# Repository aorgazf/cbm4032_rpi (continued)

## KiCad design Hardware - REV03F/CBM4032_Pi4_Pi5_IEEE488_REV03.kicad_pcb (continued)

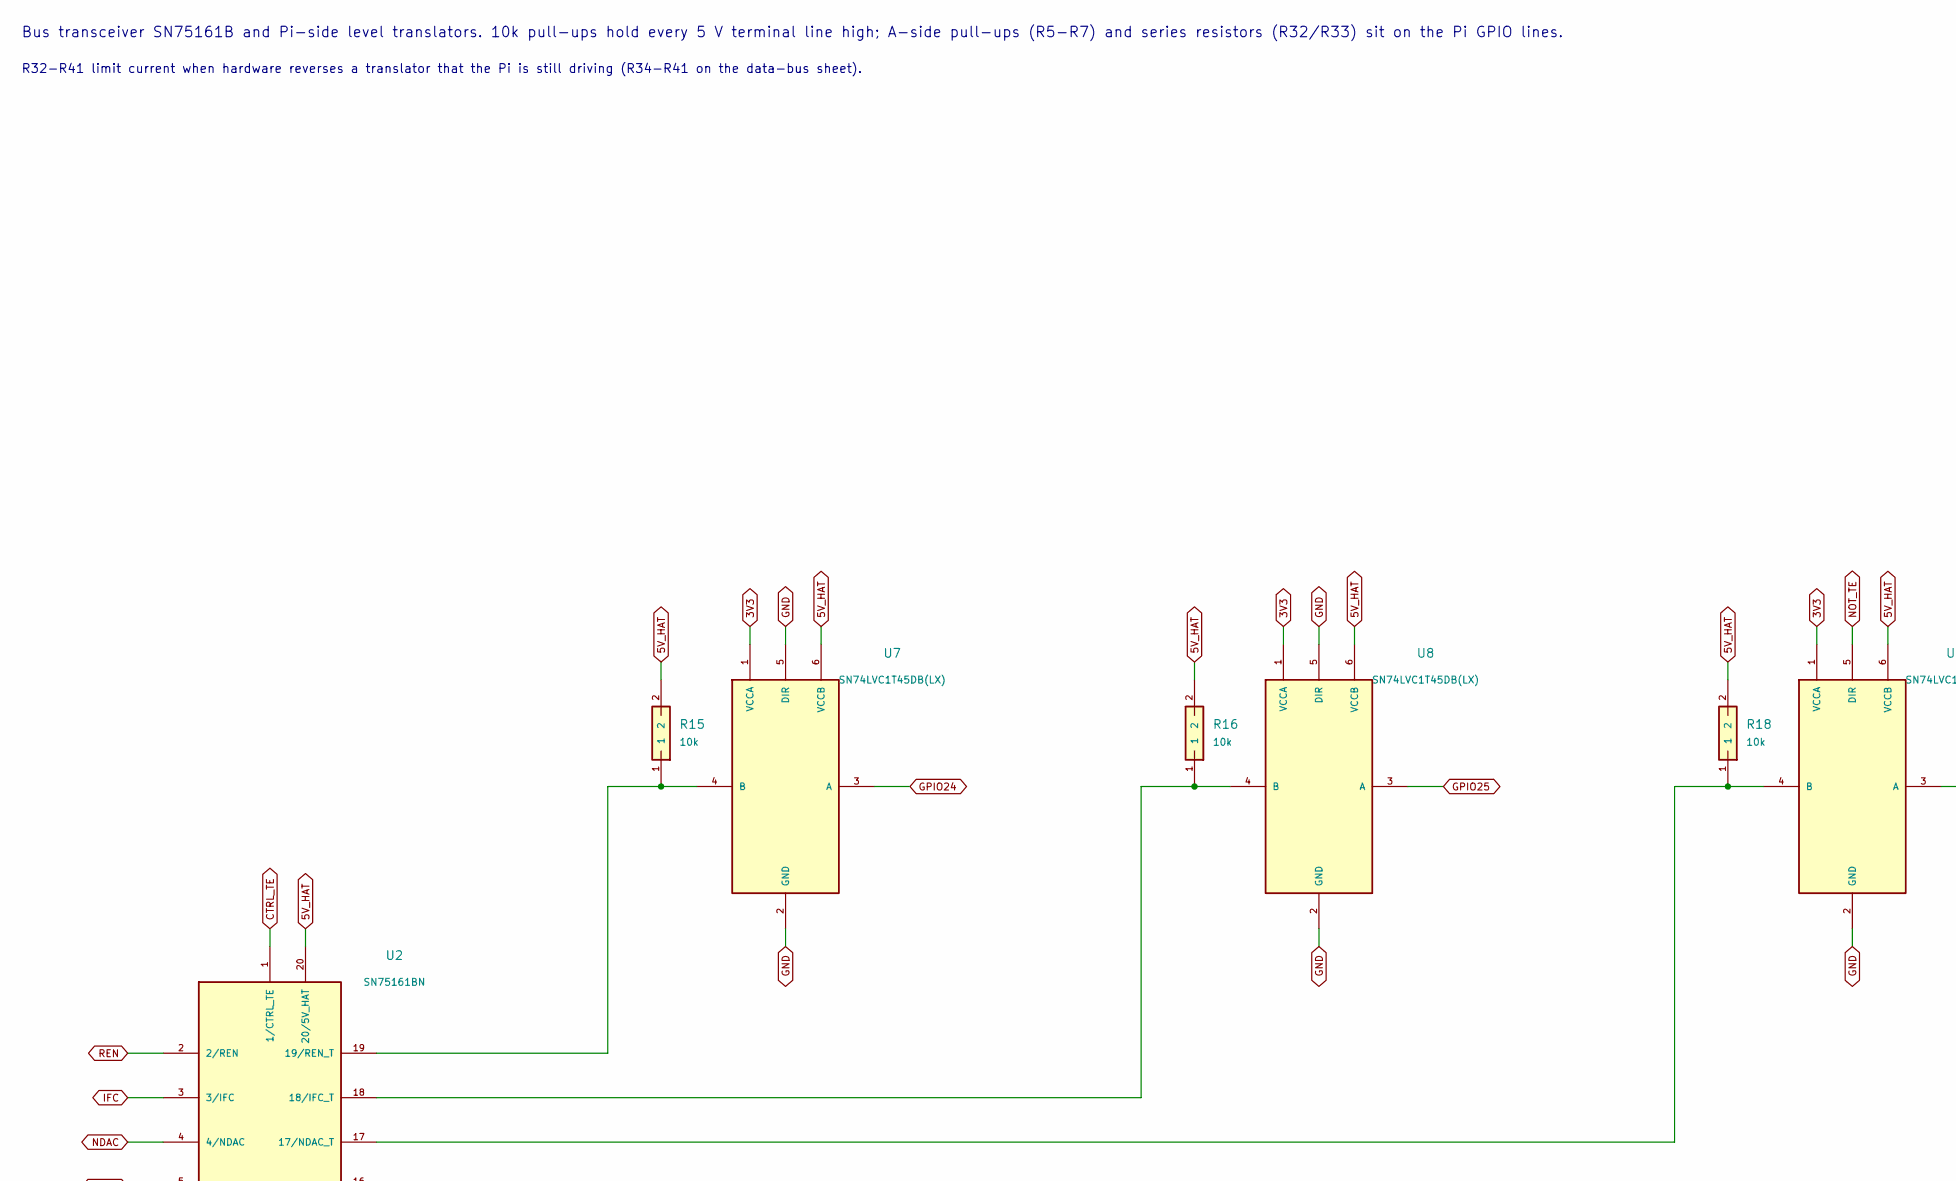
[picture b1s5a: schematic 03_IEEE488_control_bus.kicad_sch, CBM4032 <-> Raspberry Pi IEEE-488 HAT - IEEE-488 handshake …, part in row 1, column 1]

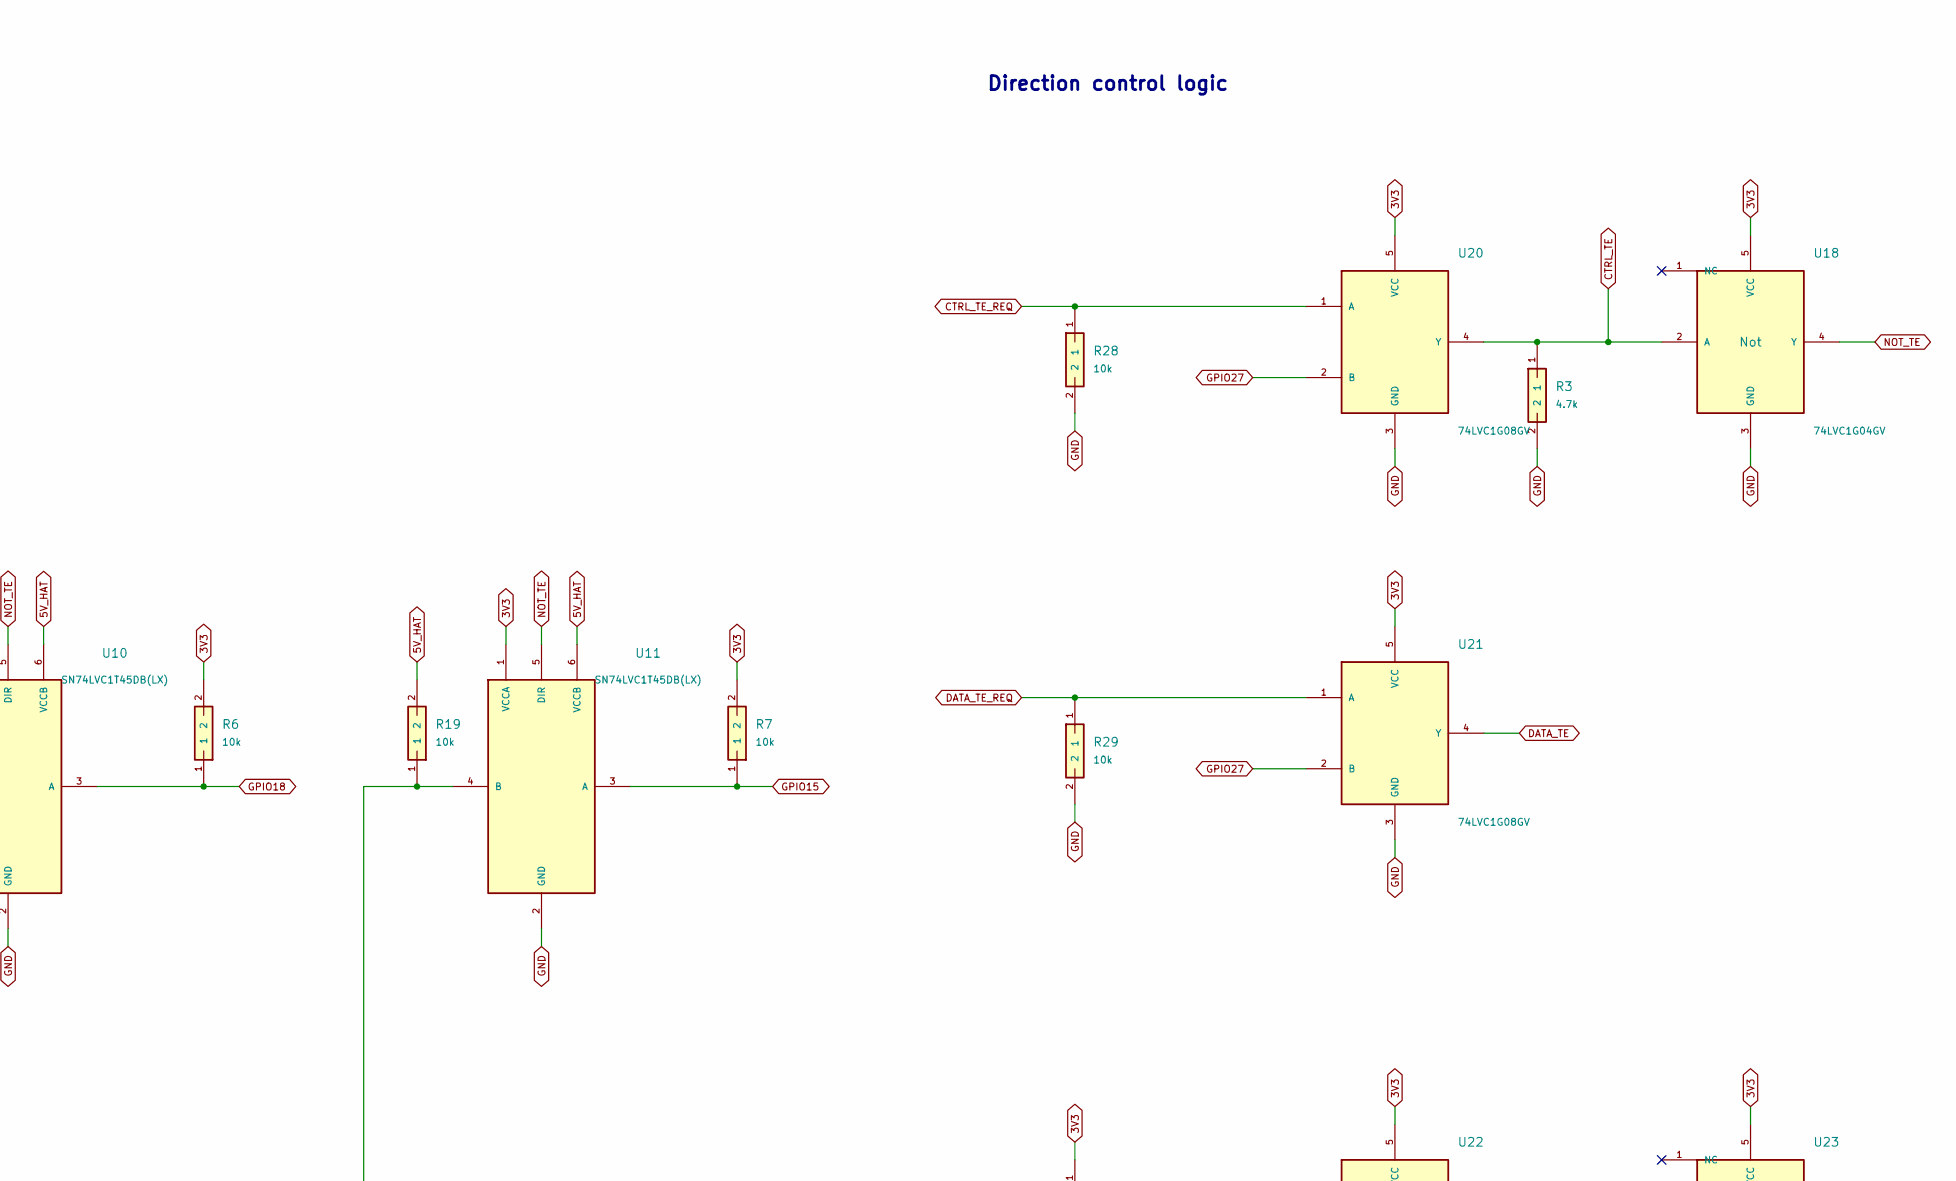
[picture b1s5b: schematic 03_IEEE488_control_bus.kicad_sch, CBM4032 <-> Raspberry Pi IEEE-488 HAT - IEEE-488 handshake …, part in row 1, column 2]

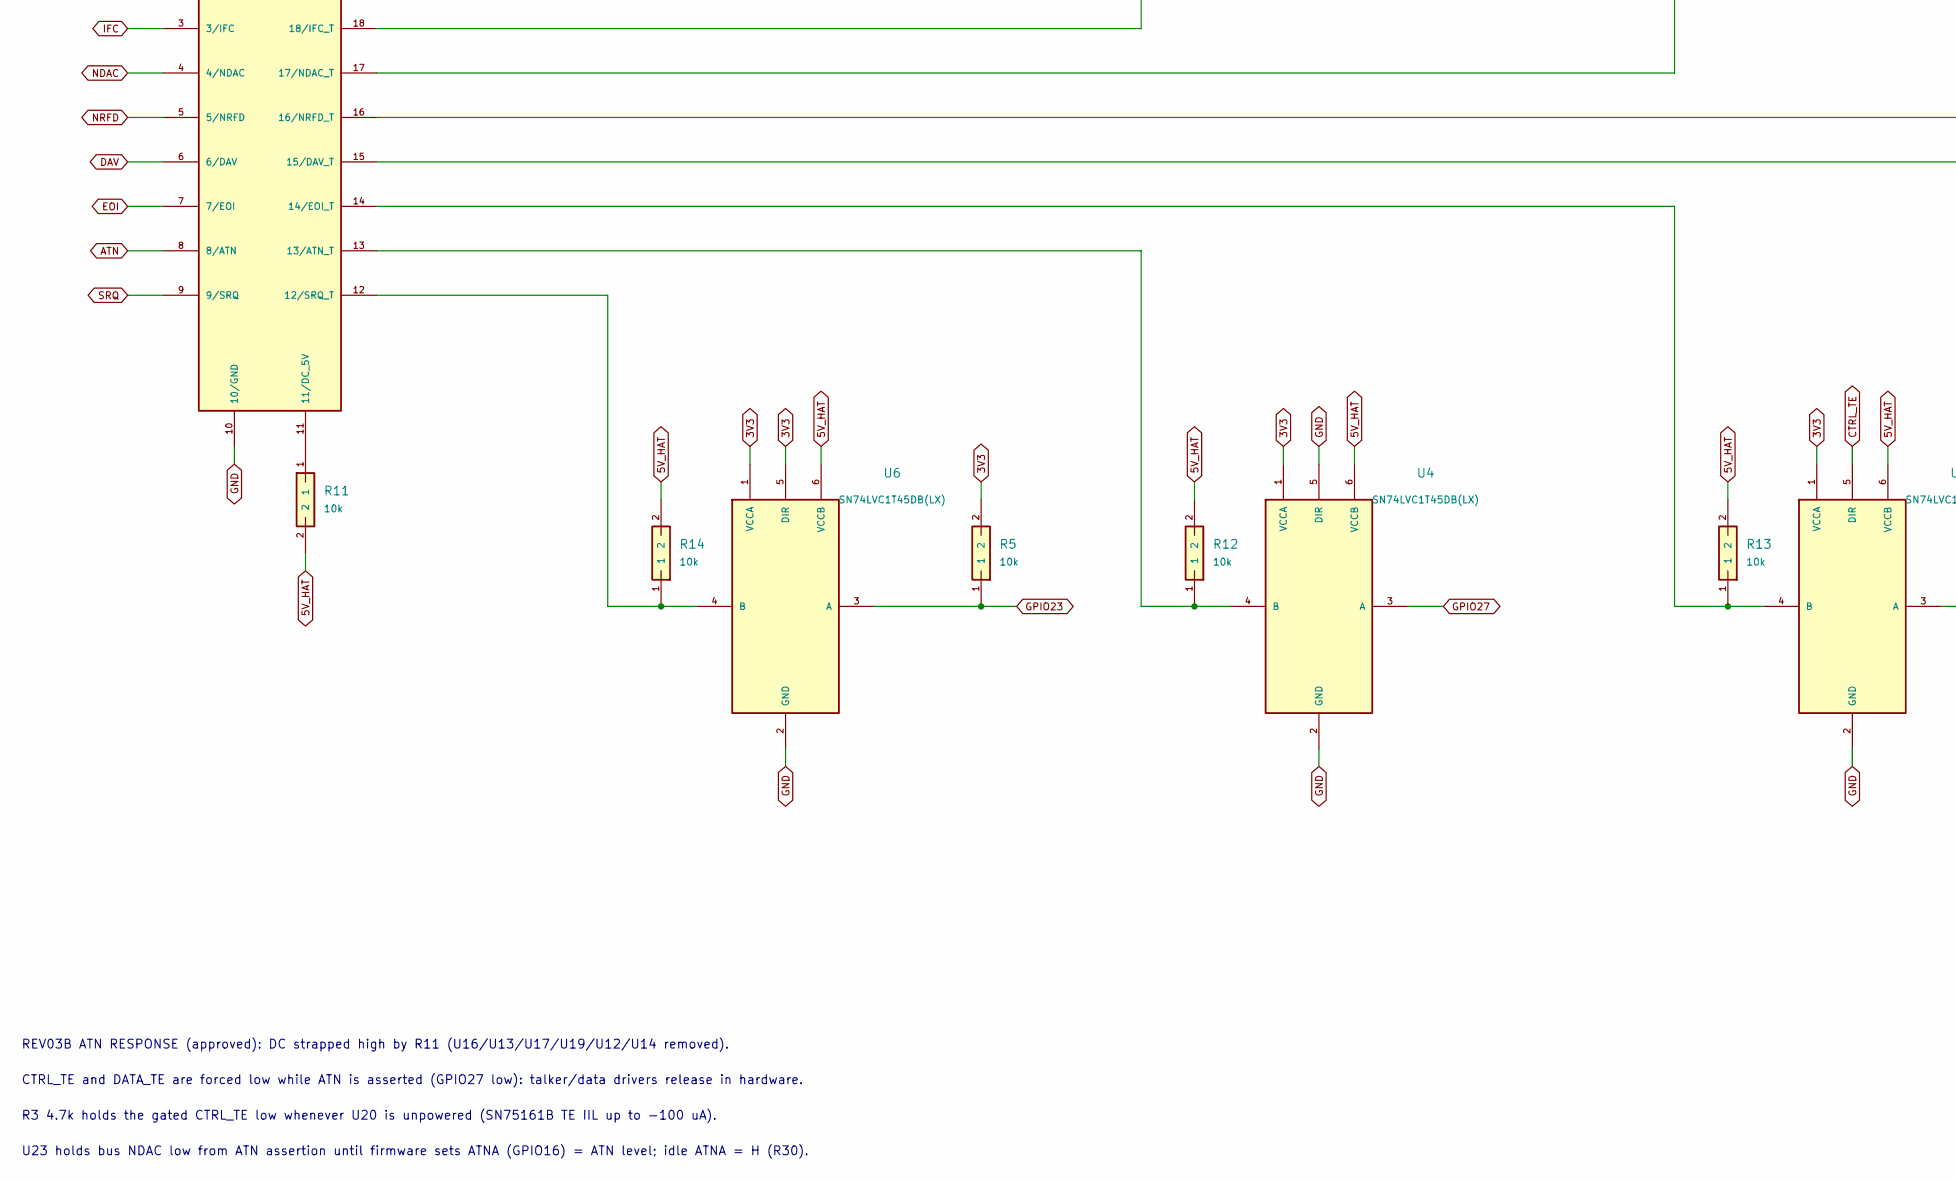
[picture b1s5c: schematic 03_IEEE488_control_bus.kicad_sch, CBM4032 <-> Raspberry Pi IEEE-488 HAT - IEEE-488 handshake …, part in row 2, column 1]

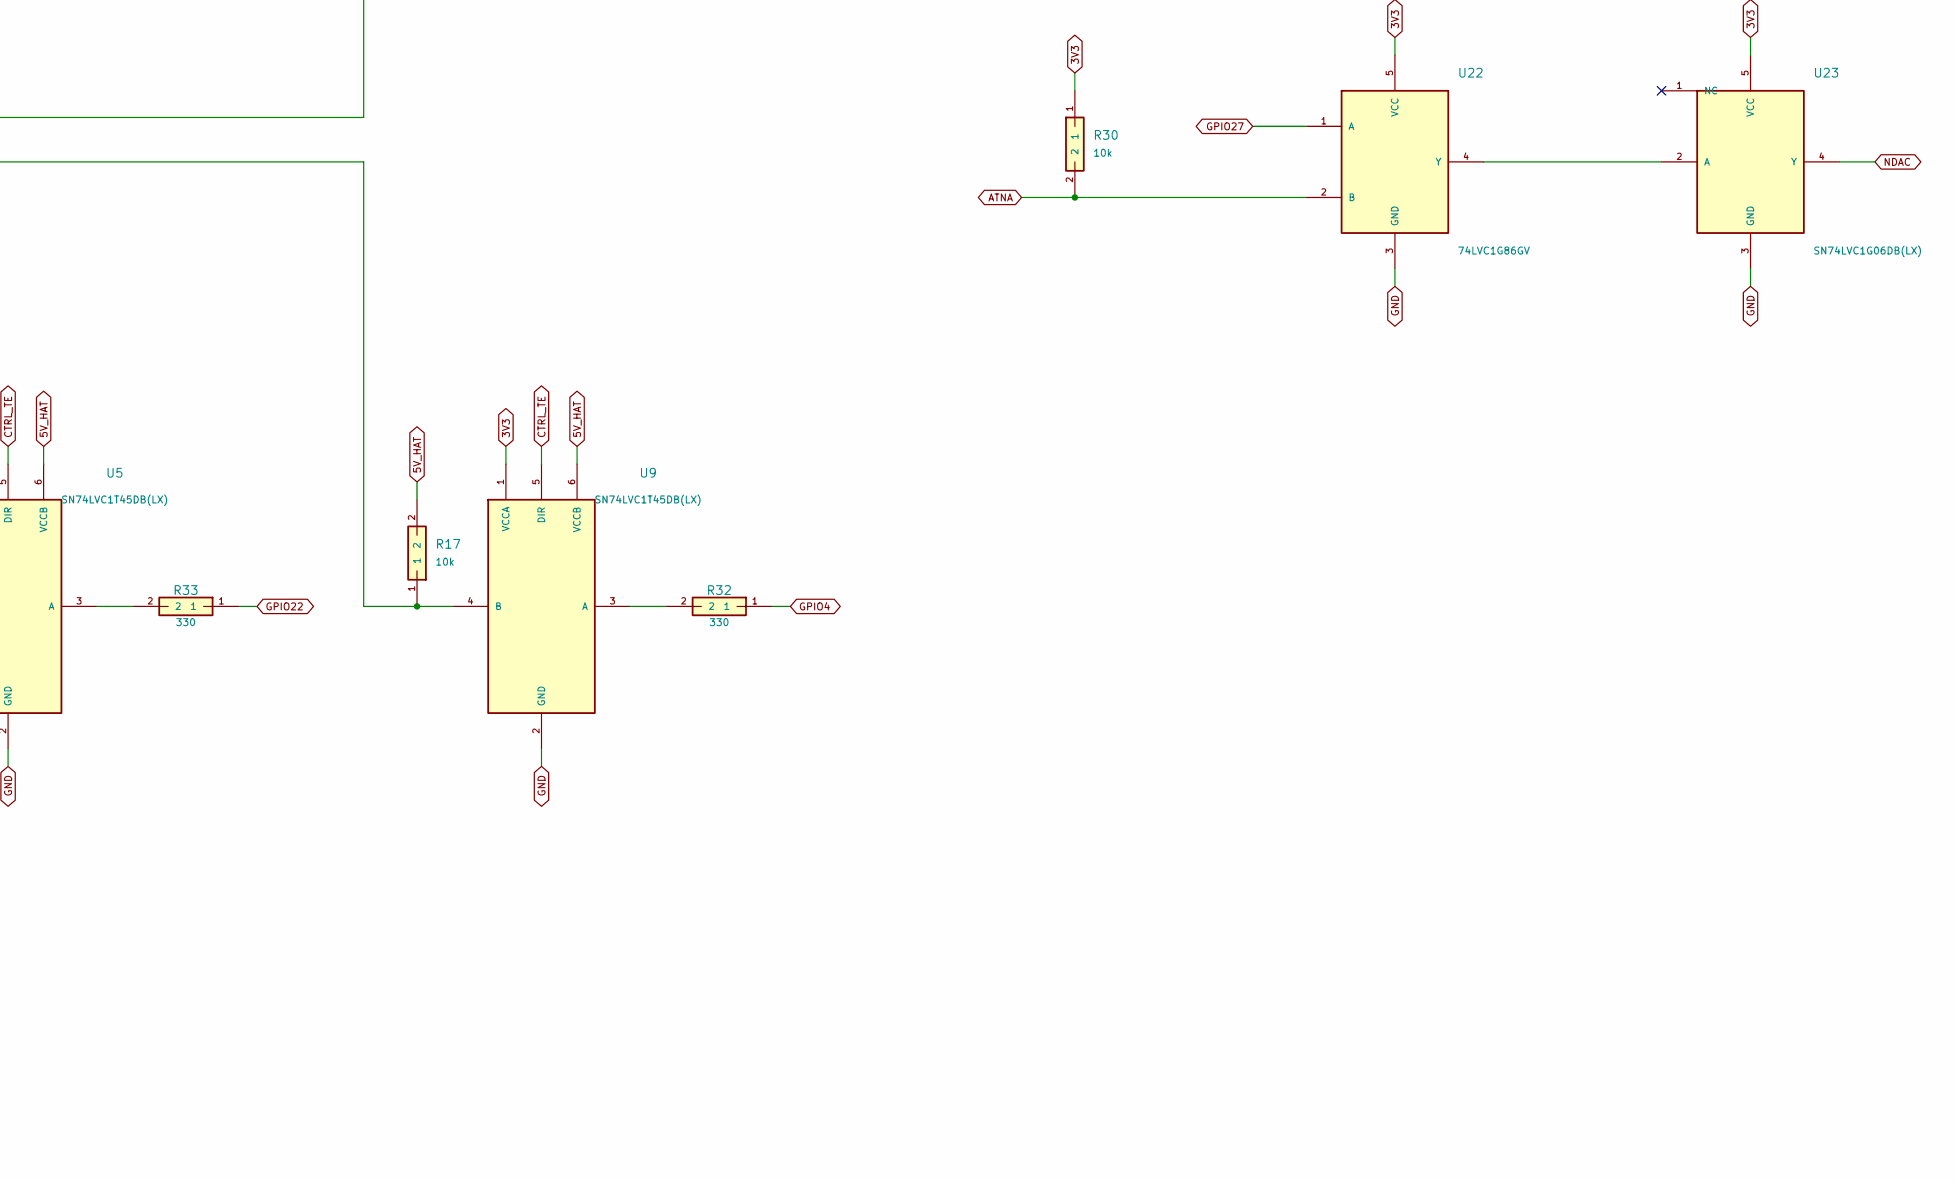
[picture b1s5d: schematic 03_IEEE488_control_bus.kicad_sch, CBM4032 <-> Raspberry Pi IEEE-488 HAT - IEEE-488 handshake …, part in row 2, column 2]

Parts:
R3: 4.7k; R0805; MPN 0805W8F4701T5E; LCSC C17673
R5, R6, R7, R11, R12, R13, R14, R15, R16, R17, R18, R19, R28, R29, R30: 10k; R0805; MPN 0805W8F1002T5E; LCSC C17414
R32, R33: 330; R0805; MPN 0805W8F3300T5E; LCSC C17630
U2: SN75161BN; DIP20; MPN SN75161BN
U4, U5, U6, U7, U8, U9, U10, U11: SN74LVC1T45DB(LX); SOT23_6; MPN SN74LVC1T45DB(LX); LCSC C22469931
U18: 74LVC1G04GV; SOT23_5; MPN 74LVC1G04GV; LCSC C19829589
U20, U21: 74LVC1G08GV; SOT23_5; MPN 74LVC1G08GV; LCSC C19829591
U22: 74LVC1G86GV; SOT23_5; MPN 74LVC1G86GV; LCSC C19829595
U23: SN74LVC1G06DB(LX); SOT23_5; MPN SN74LVC1G06DB(LX); LCSC C22469967

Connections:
3V3: R5.2, R6.2, R7.2, R30.1, U4.1 (VCCA), U5.1 (VCCA), U6.1 (VCCA), U6.5 (DIR), U7.1 (VCCA), U8.1 (VCCA), U9.1 (VCCA), U10.1 (VCCA), U11.1 (VCCA), U18.5 (VCC), U20.5 (VCC), U21.5 (VCC), U22.5 (VCC), U23.5 (VCC); also elsewhere on the board
5V_HAT: R11.2, R12.2, R13.2, R14.2, R15.2, R16.2, R17.2, R18.2, R19.2, U2.20 (20/5V_HAT), U4.6 (VCCB), U5.6 (VCCB), U6.6 (VCCB), U7.6 (VCCB), U8.6 (VCCB), U9.6 (VCCB), U10.6 (VCCB), U11.6 (VCCB); also elsewhere on the board
ATN: U2.8 (8/ATN); also elsewhere on the board
ATNA: R30.2, U22.2 (B); also elsewhere on the board
CTRL_TE: R3.1, U2.1 (1/CTRL_TE), U5.5 (DIR), U9.5 (DIR), U18.2 (A), U20.4 (Y)
CTRL_TE_REQ: R28.1, U20.1 (A); also elsewhere on the board
DATA_TE: U21.4 (Y); also elsewhere on the board
DATA_TE_REQ: R29.1, U21.1 (A); also elsewhere on the board
DAV: U2.6 (6/DAV); also elsewhere on the board
EOI: U2.7 (7/EOI); also elsewhere on the board
GND: R3.2, R28.2, R29.2, U2.10 (10/GND), U4.2 (GND), U4.5 (DIR), U5.2 (GND), U6.2 (GND), U7.2 (GND), U7.5 (DIR), U8.2 (GND), U8.5 (DIR), U9.2 (GND), U10.2 (GND), U11.2 (GND), U18.3 (GND), U20.3 (GND), U21.3 (GND), U22.3 (GND), U23.3 (GND); also elsewhere on the board
GPIO4: R32.1; also elsewhere on the board
GPIO15: R7.1, U11.3 (A); also elsewhere on the board
GPIO18: R6.1, U10.3 (A); also elsewhere on the board
GPIO22: R33.1; also elsewhere on the board
GPIO23: R5.1, U6.3 (A); also elsewhere on the board
GPIO24: U7.3 (A); also elsewhere on the board
GPIO25: U8.3 (A); also elsewhere on the board
GPIO27: U4.3 (A), U20.2 (B), U21.2 (B), U22.1 (A); also elsewhere on the board
IFC: U2.3 (3/IFC); also elsewhere on the board
NDAC: U2.4 (4/NDAC), U23.4 (Y); also elsewhere on the board
NOT_TE: U10.5 (DIR), U11.5 (DIR), U18.4 (Y)
NRFD: U2.5 (5/NRFD); also elsewhere on the board
unnamed: R11.1, U2.11 (11/DC_5V)
unnamed: R14.1, U2.12 (12/SRQ_T), U6.4 (B)
unnamed: R12.1, U2.13 (13/ATN_T), U4.4 (B)
unnamed: R13.1, U2.14 (14/EOI_T), U5.4 (B)
unnamed: R17.1, U2.15 (15/DAV_T), U9.4 (B)
unnamed: R16.1, U2.18 (18/IFC_T), U8.4 (B)
unnamed: R15.1, U2.19 (19/REN_T), U7.4 (B)
unnamed: R33.2, U5.3 (A)
unnamed: R32.2, U9.3 (A)
unnamed: R18.1, U2.17 (17/NDAC_T), U10.4 (B)
unnamed: R19.1, U2.16 (16/NRFD_T), U11.4 (B)
unnamed: U22.4 (Y), U23.2 (A)
REN: U2.2 (2/REN); also elsewhere on the board
SRQ: U2.9 (9/SRQ); also elsewhere on the board

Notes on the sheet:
Bus transceiver SN75161B and Pi-side level translators. 10k pull-ups hold every 5 V terminal line high; A-side pull-ups (R5-R7) and series resistors (R32/R33) sit on the Pi GPIO lines.
R3 4.7k holds the gated CTRL_TE low whenever U20 is unpowered (SN75161B TE IIL up to -100 uA).
REV03B ATN RESPONSE (approved): DC strapped high by R11 (U16/U13/U17/U19/U12/U14 removed).
U23 holds bus NDAC low from ATN assertion until firmware sets ATNA (GPIO16) = ATN level; idle ATNA = H (R30).
Direction control logic
R32-R41 limit current when hardware reverses a translator that the Pi is still driving (R34-R41 on the data-bus sheet).
CTRL_TE and DATA_TE are forced low while ATN is asserted (GPIO27 low): talker/data drivers release in hardware.

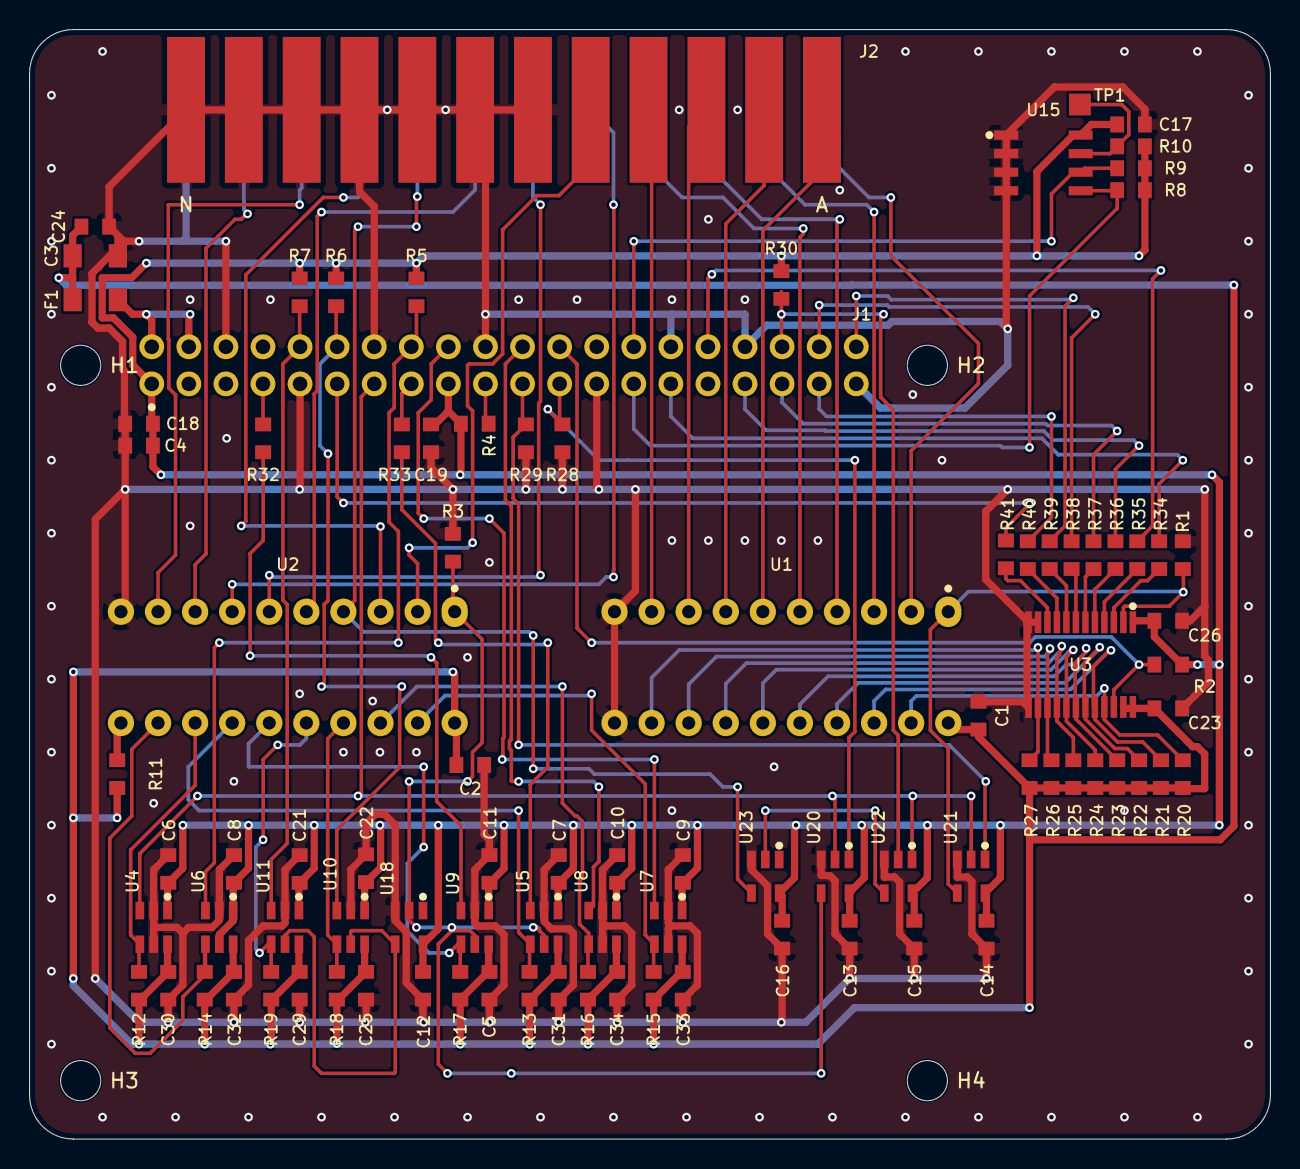
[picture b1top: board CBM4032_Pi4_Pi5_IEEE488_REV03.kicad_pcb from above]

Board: 2 copper layers, 85.0 x 76.0 mm, 96 parts (0 on the bottom side), 75 nets.

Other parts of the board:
H1, H2, H3, H4: MountingHole_2.75_NPTH

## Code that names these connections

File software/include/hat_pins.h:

/*
 * CBM 4032 IEEE-488 HAT (PCB REV03F) - GPIO map.
 *
 * Source: pad nets of Hardware - REV03F/CBM4032_Pi4_Pi5_IEEE488_REV03.kicad_pcb,
 * cross-checked against the driver brief, section 4 (see docs/HARDWARE_CHECK.md).
 *
 * Every line is non-inverting from GPIO to bus: GPIO low = bus low = asserted.
 * A bus data byte is therefore the bitwise inverse of the gathered DIO bits.
 */
#ifndef HAT_PINS_H
#define HAT_PINS_H

#include <stdint.h>

/* Data lines DIO1..DIO8 (U3 A1..A8 through R34..R41, 330 ohm) */
#define PIN_DIO1 5
#define PIN_DIO2 12
#define PIN_DIO3 13
#define PIN_DIO4 19
#define PIN_DIO5 20
#define PIN_DIO6 21
#define PIN_DIO7 26
#define PIN_DIO8 17

/* Direction control */
#define PIN_DATA_OE_N    8   /* U3 OE#, low enables the data translator; R2 pull-up */
#define PIN_DATA_TE_REQ  9   /* U21: DATA_TE = GPIO9 AND ATN; R29 pull-down */
#define PIN_CTRL_TE_REQ 11   /* U20: CTRL_TE = GPIO11 AND ATN; R28 pull-down */
#define PIN_ATNA        16   /* U22: ATN_HOLD = ATN XOR ATNA -> U23 on bus NDAC; R30 pull-up */

/* Management lines, fixed direction */
#define PIN_ATN 27           /* in, always (U4 receive) */
#define PIN_REN 24           /* in, always (U7); tied to GND on the PET */
#define PIN_IFC 25           /* in, always (U8) */
#define PIN_SRQ 23           /* out, always (U6 transmit); R5 pull-up */

/* Handshake lines, direction follows CTRL_TE */
#define PIN_DAV  4           /* out when CTRL_TE=H (U9, R32 330 ohm), else in */
#define PIN_EOI 22           /* out when CTRL_TE=H (U5, R33 330 ohm), else in */
#define PIN_NDAC 18          /* out when CTRL_TE=L (U10), else in; R6 pull-up */
#define PIN_NRFD 15          /* out when CTRL_TE=L (U11), else in; R7 pull-up */

#define PIN_SPARE 10         /* only R4 pull-up; free for a debug strobe */

#define BIT(n) (1u << (n))

#define MASK_DIO  (BIT(PIN_DIO1) | BIT(PIN_DIO2) | BIT(PIN_DIO3) | BIT(PIN_DIO4) | \
                   BIT(PIN_DIO5) | BIT(PIN_DIO6) | BIT(PIN_DIO7) | BIT(PIN_DIO8))
#define MASK_TALK_CTRL (BIT(PIN_DAV) | BIT(PIN_EOI))       /* Pi drives when CTRL_TE=H */
#define MASK_LISTEN_CTRL (BIT(PIN_NDAC) | BIT(PIN_NRFD))   /* Pi drives when CTRL_TE=L */
#define MASK_MGMT_IN (BIT(PIN_ATN) | BIT(PIN_REN) | BIT(PIN_IFC))
#define MASK_DIRCTL (BIT(PIN_DATA_OE_N) | BIT(PIN_DATA_TE_REQ) | BIT(PIN_CTRL_TE_REQ) | BIT(PIN_ATNA))

/* Every GPIO the driver touches (GPIO10 is added only by tools that use it) */
#define MASK_HAT (MASK_DIO | MASK_TALK_CTRL | MASK_LISTEN_CTRL | MASK_MGMT_IN | \
                  BIT(PIN_SRQ) | MASK_DIRCTL)

static const uint8_t hat_dio_pin[8] = {
    PIN_DIO1, PIN_DIO2, PIN_DIO3, PIN_DIO4, PIN_DIO5, PIN_DIO6, PIN_DIO7, PIN_DIO8
};

/* J2 (PET edge connector) contact for each signal, for messages */
#define J2_DIO1 "1"
#define J2_EOI  "5"
#define J2_DAV  "6"
#define J2_NRFD "7"
#define J2_NDAC "8"
#define J2_IFC  "9"
#define J2_SRQ  "10"
#define J2_ATN  "11"
#define J2_REN  "E"
static const char *const hat_dio_j2[8] = { "1", "2", "3", "4", "A", "B", "C", "D" };

/*
 * Gather DIO1..8 from a raw level word into bits 0..7 (still raw: 1 = high
 * = released). Shift distances follow the pin numbers above.
 */
static inline uint8_t hat_dio_gather(uint32_t raw)
{
    return (uint8_t)(((raw >> 5) & 0x01) |   /* GPIO5  -> bit 0 */
                     ((raw >> 11) & 0x02) |  /* GPIO12 -> bit 1 */
                     ((raw >> 11) & 0x04) |  /* GPIO13 -> bit 2 */
                     ((raw >> 16) & 0x08) |  /* GPIO19 -> bit 3 */
                     ((raw >> 16) & 0x10) |  /* GPIO20 -> bit 4 */
                     ((raw >> 16) & 0x20) |  /* GPIO21 -> bit 5 */
                     ((raw >> 20) & 0x40) |  /* GPIO26 -> bit 6 */
                     ((raw >> 10) & 0x80));  /* GPIO17 -> bit 7 */
}

/* Bus byte (IEEE-488 logical value, 1 = asserted = low) from a raw level word */
static inline uint8_t hat_bus_byte(uint32_t raw)
{
    return (uint8_t)~hat_dio_gather(raw);
}

/*
 * Pin masks to put a bus byte on DIO1..8: bits that are 1 in the byte are
 * asserted, so they go in the clear mask; the rest go in the set mask.
 */
extern uint32_t hat_dio_spread[256];   /* byte bit i -> GPIO bit hat_dio_pin[i] */
void hat_pins_init(void);              /* fills hat_dio_spread[] */

static inline uint32_t hat_byte_clr_mask(uint8_t bus_byte) { return hat_dio_spread[bus_byte]; }
static inline uint32_t hat_byte_set_mask(uint8_t bus_byte) { return hat_dio_spread[(uint8_t)~bus_byte]; }

#endif

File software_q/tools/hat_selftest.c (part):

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static int preflight(int force)
{
    uint32_t raw = gpio_read(g);
    if (!lvl(raw, PIN_REN) || !lvl(raw, PIN_IFC) || !lvl(raw, PIN_ATN)) {
        printf("REN, IFC or ATN reads asserted (raw 0x%07x): the HAT looks plugged into a PET.\n"
               "Active tests drive bus lines. Unplug the HAT, or use --read-only.%s\n",
               raw, force ? " (--force given: continuing)" : "");
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
    puts("T0  Idle levels from the board pulls (before the test configures anything)");
    r = gpio_read(g);
    check("GPIO8 DATA_OE_N high (R2 / config.txt): U3 disabled", lvl(r, PIN_DATA_OE_N), "R2, J1-24");
    check("GPIO9 DATA_TE_REQ low (R29)", !lvl(r, PIN_DATA_TE_REQ), "R29, J1-21; or a program left it high: run hat_safe");
    check("GPIO11 CTRL_TE_REQ low (R28)", !lvl(r, PIN_CTRL_TE_REQ), "R28, J1-23; or run hat_safe");
    check("GPIO16 ATNA high (R30)", lvl(r, PIN_ATNA), "R30, J1-36");
    check("GPIO18 NDAC, GPIO15 NRFD high (R6, R7)", lvl(r, PIN_NDAC) && lvl(r, PIN_NRFD), "R6/R7, U10/U11");
    check("GPIO23 SRQ high (R5)", lvl(r, PIN_SRQ), "R5, U6");
    check("GPIO10 spare high (R4)", lvl(r, PIN_SPARE), "R4, J1-19");
    check("GPIO27 ATN, GPIO24 REN, GPIO25 IFC released", lvl(r, PIN_ATN) && lvl(r, PIN_REN) && lvl(r, PIN_IFC),
          "U2 receive path, U4/U7/U8, R12/R15/R16, 5V_HAT and F1");
    check("GPIO4 DAV, GPIO22 EOI released (U9/U5 receive)", lvl(r, PIN_DAV) && lvl(r, PIN_EOI),
          "U9/U5 direction (CTRL_TE low via R3), R32/R33, U2");

    hat_configure(g);
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    puts("T2  Control talk enable (U20) and translator direction (U5, U9, U10, U11)");
    g->set_pull(g, MASK_TALK_CTRL, GPIO_PULL_DOWN);
    r = rd();
    check("GPIO11 low: GPIO4/22 driven high by U9/U5 against the Pi pull-down",
          lvl(r, PIN_DAV) && lvl(r, PIN_EOI), "U9/U5 not driving the A side: DIR stuck high? CTRL_TE, R3, U20");
    gpio_set(g, BIT(PIN_CTRL_TE_REQ));
    r = rd();
    check("GPIO11 high: GPIO4/22 follow the Pi pull-down (U9/U5 turned A->B)",
          !lvl(r, PIN_DAV) && !lvl(r, PIN_EOI), "CTRL_TE not granted: U20 (GPIO11 AND GPIO27), R28, U9/U5 DIR");
    check("GPIO11 high: GPIO18/15 read released bus NDAC/NRFD (U10/U11 turned B->A)",
          lvl(r, PIN_NDAC) && lvl(r, PIN_NRFD), "U18 inverter, U10/U11 DIR, U2 NDAC/NRFD receive");

    puts("T3  NDAC hold (U22 XOR, U23 open drain) read back through U2 and U10");
    gpio_clr(g, BIT(PIN_ATNA));
    r = rd();
    check("ATN released, GPIO16 low: bus NDAC held low, seen on GPIO18", !lvl(r, PIN_NDAC),
          "U22 (GPIO27 XOR GPIO16), U23 output to bus NDAC (J2-8), U2 pin 4/17, U10");
    check("NRFD unaffected", lvl(r, PIN_NRFD), "short between NDAC and NRFD paths?");
    gpio_set(g, BIT(PIN_ATNA));
    r = rd();
    check("GPIO16 high again: bus NDAC released", lvl(r, PIN_NDAC), "U22/U23 stuck");
    gpio_clr(g, BIT(PIN_CTRL_TE_REQ));
    g->set_pull(g, MASK_TALK_CTRL, GPIO_PULL_UP);
    r = rd();
    check("GPIO11 low again: GPIO4/22 driven high by U9/U5", lvl(r, PIN_DAV) && lvl(r, PIN_EOI), "U20/U9/U5");

    puts("T4  Data talk enable (U21) and U3 direction");
    g->set_pull(g, MASK_DIO, GPIO_PULL_DOWN);
    r = rd();
    check_dio("GPIO9 low: DIO driven high by U3 against the Pi pull-down", r, 1, "U3 B->A outputs, R34-R41");
    gpio_set(g, BIT(PIN_DATA_TE_REQ));
    r = rd();
    check_dio("GPIO9 high: DIO follow the Pi pull-down (U3 turned A->B)", r, 0,
              "DATA_TE not granted: U21 (GPIO9 AND GPIO27), R1, U3 pin 2; or pin shorted high");
    g->set_pull(g, MASK_DIO, GPIO_PULL_UP);
    r = rd();
    check_dio("GPIO9 high, Pi pull-up: DIO read high (no pin shorted low)", r, 1, "short to GND near U3 A side or R34-R41");
    gpio_clr(g, BIT(PIN_DATA_TE_REQ));
    gpio_set(g, BIT(PIN_DATA_OE_N));
    g->set_pull(g, MASK_DIO, GPIO_PULL_DOWN);
    r = rd();
    check_dio("GPIO8 high: U3 disabled, DIO follow the Pi pull-down", r, 0, "U3 OE# (pin 22) stuck low? R2");
    g->set_pull(g, MASK_DIO, GPIO_PULL_UP);
    gpio_clr(g, BIT(PIN_DATA_OE_N));

    puts("T5  SRQ output pad");
    gpio_clr(g, BIT(PIN_SRQ));
    g->make_output(g, BIT(PIN_SRQ));
    r = rd();
    check("GPIO23 driven low reads low", !lvl(r, PIN_SRQ), "GPIO23 shorted to 3V3?");
    gpio_set(g, BIT(PIN_SRQ));
    g->make_input(g, BIT(PIN_SRQ));

    hat_safe_state(g);
    puts("\nNot covered here: bus-side drive of each output (use --manual with a meter) and the"
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{
    hat_configure(g);
    probe_line_t rx[13] = {
        { PIN_ATN, "ATN", J2_ATN }, { PIN_REN, "REN", J2_REN }, { PIN_IFC, "IFC", J2_IFC },
        { PIN_DAV, "DAV", J2_DAV }, { PIN_EOI, "EOI", J2_EOI },
    };
    static const char *dn[8] = { "DIO1", "DIO2", "DIO3", "DIO4", "DIO5", "DIO6", "DIO7", "DIO8" };
    for (int i = 0; i < 8; i++) rx[5 + i] = (probe_line_t){ hat_dio_pin[i], dn[i], hat_dio_j2[i] };
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    puts("\nPhase 2: ATN withdraws the talk enables (U20, U21). Both enables are now requested, so\n"
         "DAV, EOI and DIO are driven low on J2. Touch ONLY contact 11 (ATN) to ground.");
    g->set_pull(g, MASK_TALK_CTRL | MASK_DIO, GPIO_PULL_DOWN);
    gpio_set(g, BIT(PIN_CTRL_TE_REQ) | BIT(PIN_DATA_TE_REQ));
    {
        int ok_ctrl = 0, ok_data = 0;
        while (!stop && !(ok_ctrl && ok_data)) {
            uint32_t r = gpio_read(g);
            if (!lvl(r, PIN_ATN)) {
                ok_ctrl |= lvl(r, PIN_DAV) && lvl(r, PIN_EOI);
                ok_data |= (hat_dio_gather(r) == 0xFF);
            }
            if (enter_pressed(20)) break;
        }
        check("ATN low forces CTRL_TE low (GPIO4/22 driven by U9/U5 again)", ok_ctrl, "U20 gate, GPIO27 net");
        check("ATN low forces DATA_TE low (DIO driven by U3 again)", ok_data, "U21 gate, U3 DIR");
    }
    gpio_clr(g, BIT(PIN_CTRL_TE_REQ) | BIT(PIN_DATA_TE_REQ));
    g->set_pull(g, MASK_TALK_CTRL | MASK_DIO, GPIO_PULL_UP);
    if (stop) goto out;

    puts("\nPhase 3: talker direction for NRFD/NDAC. DAV and EOI are now actively driven high:\n"
         "touch ONLY contacts 7 (NRFD) and 8 (NDAC) to ground.");
    gpio_set(g, BIT(PIN_CTRL_TE_REQ));
    probe_line_t hs[2] = { { PIN_NRFD, "NRFD", J2_NRFD }, { PIN_NDAC, "NDAC", J2_NDAC } };
    probe_phase(hs, 2);
out:
    hat_safe_state(g);
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    hat_configure(g);
    if (ask("IDLE: J2 contacts 1-11 and A-E all HIGH") < 0) goto out;

    gpio_clr(g, BIT(PIN_SRQ));
    g->make_output(g, BIT(PIN_SRQ));
    if (ask("SRQ asserted: J2-10 LOW, others HIGH") < 0) goto out;
    gpio_set(g, BIT(PIN_SRQ));
    g->make_input(g, BIT(PIN_SRQ));

    gpio_clr(g, BIT(PIN_NRFD));
    g->make_output(g, BIT(PIN_NRFD));
    if (ask("NRFD asserted (GPIO15 low): J2-7 LOW, others HIGH") < 0) goto out;
    gpio_set(g, BIT(PIN_NRFD));
    g->make_input(g, BIT(PIN_NRFD));

    gpio_clr(g, BIT(PIN_NDAC));
    g->make_output(g, BIT(PIN_NDAC));
    if (ask("NDAC asserted (GPIO18 low): J2-8 LOW, others HIGH") < 0) goto out;
    gpio_set(g, BIT(PIN_NDAC));
    g->make_input(g, BIT(PIN_NDAC));

    gpio_clr(g, BIT(PIN_ATNA));
    if (ask("NDAC hold (GPIO16 low, ATN released): J2-8 LOW, others HIGH") < 0) goto out;
    gpio_set(g, BIT(PIN_ATNA));

    hat_become_talker(g);
    if (ask("TALKER idle: J2 contacts 1-11 and A-E all HIGH") < 0) goto out;
    gpio_clr(g, BIT(PIN_DAV));
    if (ask("DAV asserted: J2-6 LOW, others HIGH") < 0) goto out;
    gpio_set(g, BIT(PIN_DAV));
    gpio_clr(g, BIT(PIN_EOI));
    if (ask("EOI asserted: J2-5 LOW, others HIGH") < 0) goto out;
    gpio_set(g, BIT(PIN_EOI));
    for (int i = 0; i < 8; i++) {
        uint8_t b = (uint8_t)(1 << i);
        gpio_write(g, hat_byte_set_mask(b), hat_byte_clr_mask(b));
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    hat_decode(r, &l);
    int data_valid = !l.oe_n && !l.data_te_req;
    printf("raw 0x%07x\n", r);
    printf("  ATN  %-8s GPIO27   REN %-8s GPIO24 (always asserted on a PET)   IFC %-8s GPIO25\n",
           l.atn ? "asserted" : "released", l.ren ? "asserted" : "released", l.ifc ? "asserted" : "released");
    printf("  DAV  %-8s GPIO4    EOI %-8s GPIO22   (bus values while GPIO11 is low)\n",
           l.dav ? "asserted" : "released", l.eoi ? "asserted" : "released");
    printf("  NDAC %-8s GPIO18   NRFD %-8s GPIO15  (own outputs while GPIO11 is low)\n",
           l.ndac ? "low" : "high", l.nrfd ? "low" : "high");
    printf("  SRQ  %-8s GPIO23   ATNA %s   CTRL_TE_REQ %d   DATA_TE_REQ %d   DATA_OE_N %d\n",
           l.srq ? "asserted" : "released", l.atna_low ? "low (software holds NDAC)" : "high",
           l.ctrl_te_req, l.data_te_req, l.oe_n);
    if (data_valid) printf("  DATA $%02X\n", l.data);
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{
    if (rx) {
        uint32_t r = gpio_read(g);
        if (lvl(r, PIN_DATA_TE_REQ) || (g->output_mask(g) & MASK_DIO)) {
            puts("--rx refused: GPIO9 is high or a DIO pin is an output (another program running?)");
            return;
        }
        gpio_clr(g, BIT(PIN_DATA_OE_N));
        g->claim(g, BIT(PIN_DATA_OE_N));
        g->make_output(g, BIT(PIN_DATA_OE_N));
    }
    uint32_t prev = ~0u;
    char buf[64];
    print_state(gpio_read(g));
    while (watch && !stop) {
        uint32_t r = gpio_read(g) & (MASK_HAT & ~BIT(PIN_DATA_OE_N));
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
